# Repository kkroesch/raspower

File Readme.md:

# RasPower

Powering Raspberry Pi (starting from Mode 3) in a device where DC power is already available.
The circuit provides reverse polarity protection, overvoltage protection, and filtering of high-frequency interference into the power supply, and it prevents backfeeding from the powered device.

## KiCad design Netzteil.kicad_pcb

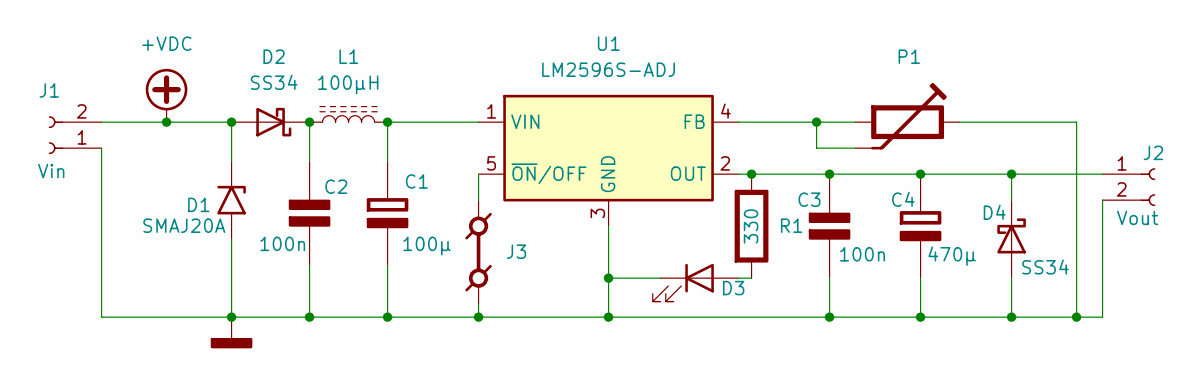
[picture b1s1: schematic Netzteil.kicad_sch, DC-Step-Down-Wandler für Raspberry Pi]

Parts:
C1: 100µ; CP_EIA-3528-12_Kemet-T; Rating V
C2, C3: 100n; C_0603_1608Metric; Rating V
C4: 470µ; CP_EIA-3528-12_Kemet-T; Rating V
D1: SMAJ20A; D_SMA
D2, D4: SS34; D_SMA
D3: LED; LED_Kingbright_AAA3528ESGCT
J1: Vin; TerminalBlock_Phoenix_MPT-0,5-2-2.54_1x02_P2.54mm_Horizontal
J2: Vout; TerminalBlock_Phoenix_MPT-0,5-2-2.54_1x02_P2.54mm_Horizontal
J3: J-jumper; PinHeader_1x02_P2.54mm_Vertical
L1: 100µH; L_Radial_D7.5mm_P5.00mm_Fastron_07P
P1: P-trim; Potentiometer_Bourns_3386P_Vertical
R1: 330; R_MiniMELF_MMA-0204; Rating W
U1: LM2596S-ADJ; TO-263-5_TabPin3

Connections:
+VDC: D1.1 (A1), D2.2 (A), J1.2
unnamed: C1.1 (+), L1.2, U1.1 (VIN)
unnamed: C2.1 (+), D2.1 (K), L1.1
unnamed: C3.1 (+), C4.1 (+), D4.1 (K), J2.1, R1.1 (+), U1.2 (OUT)
unnamed: D3.2 (A), R1.2 (-)
unnamed: P1.1 (a), P1.2 (b), U1.4 (FB)
unnamed: J3.1, U1.5 (~ON/OFF)
V-GND: C1.2 (-), C2.2 (-), C3.2 (-), C4.2 (-), D1.2 (A2), D3.1 (K), D4.2 (A), J1.1, J2.2, J3.2, P1.3 (c), U1.3 (GND)

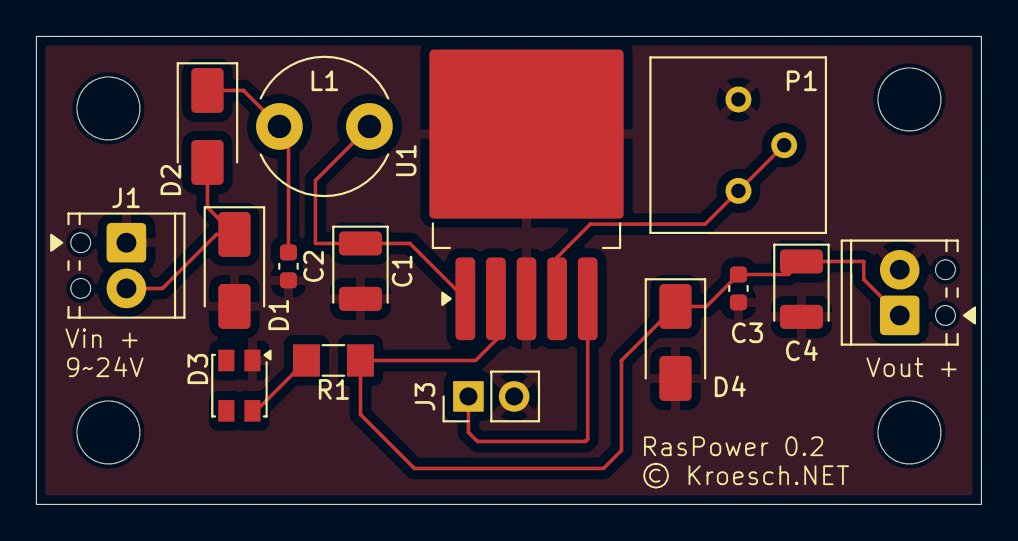
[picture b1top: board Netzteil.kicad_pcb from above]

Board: 2 copper layers, 52.5 x 26.0 mm, 15 parts (0 on the bottom side), 8 nets.

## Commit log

2025-05-04 First Draft.
2025-05-04 Added Footprints.
2025-05-04 First Layout Draft.
2025-05-04 First Routes.
2025-05-04 Second try routing.
2025-05-04 Moved backup from git.
2025-05-04 Added Readme.
2025-05-04 PCB design correction
2025-05-04 Design correction
2025-05-05 Added workflow

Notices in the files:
Netzteil.kicad_pcb:
© Kroesch.NET
